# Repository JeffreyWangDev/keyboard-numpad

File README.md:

# Keyboard PCB Repository

This contains files and resources to design and build custom keyboard PCBs using KiCad.

## Getting Started

1. **Clone the Repository**:
    ```sh
    git clone https://github.com/jeffreywangdev/keyboard-numpad.git
    cd keyboard-numpad
    ```
2. **Install KiCad**: Ensure the latest version is installed.
3. **Open the Project**: Open the `.kicad_pro` file.
4. **Explore the Libraries**: Check out the footprint libraries and 3D models.

## Directory Structure

```
keyboard-numpad/
├── 3dmodels/                # 3D models
├── footprints/              # Footprint libraries
├── symbols/                 # Symbol libraries
├── docs/                    # Documentation
```

## Contributing

1. **Fork the Repository**: On GitHub.
2. **Create a Branch**:
    ```sh
    git checkout -b feature-name
    ```
3. **Make Changes**: Commit with descriptive messages.
4. **Submit a Pull Request**: Merge changes into the main repository.

## License

Licensed under the MIT License. See the [LICENSE](LICENSE) file.

Happy designing!

## Code
https://github.com/JeffreyWangDev/qmk_firmware/commit/e154b066790265e3da3770a5a3616bc74e3c47f7#diff-a4a6e8d4f2de04b7d767e970e2a342e9860d40d9419f873e876addc308344293

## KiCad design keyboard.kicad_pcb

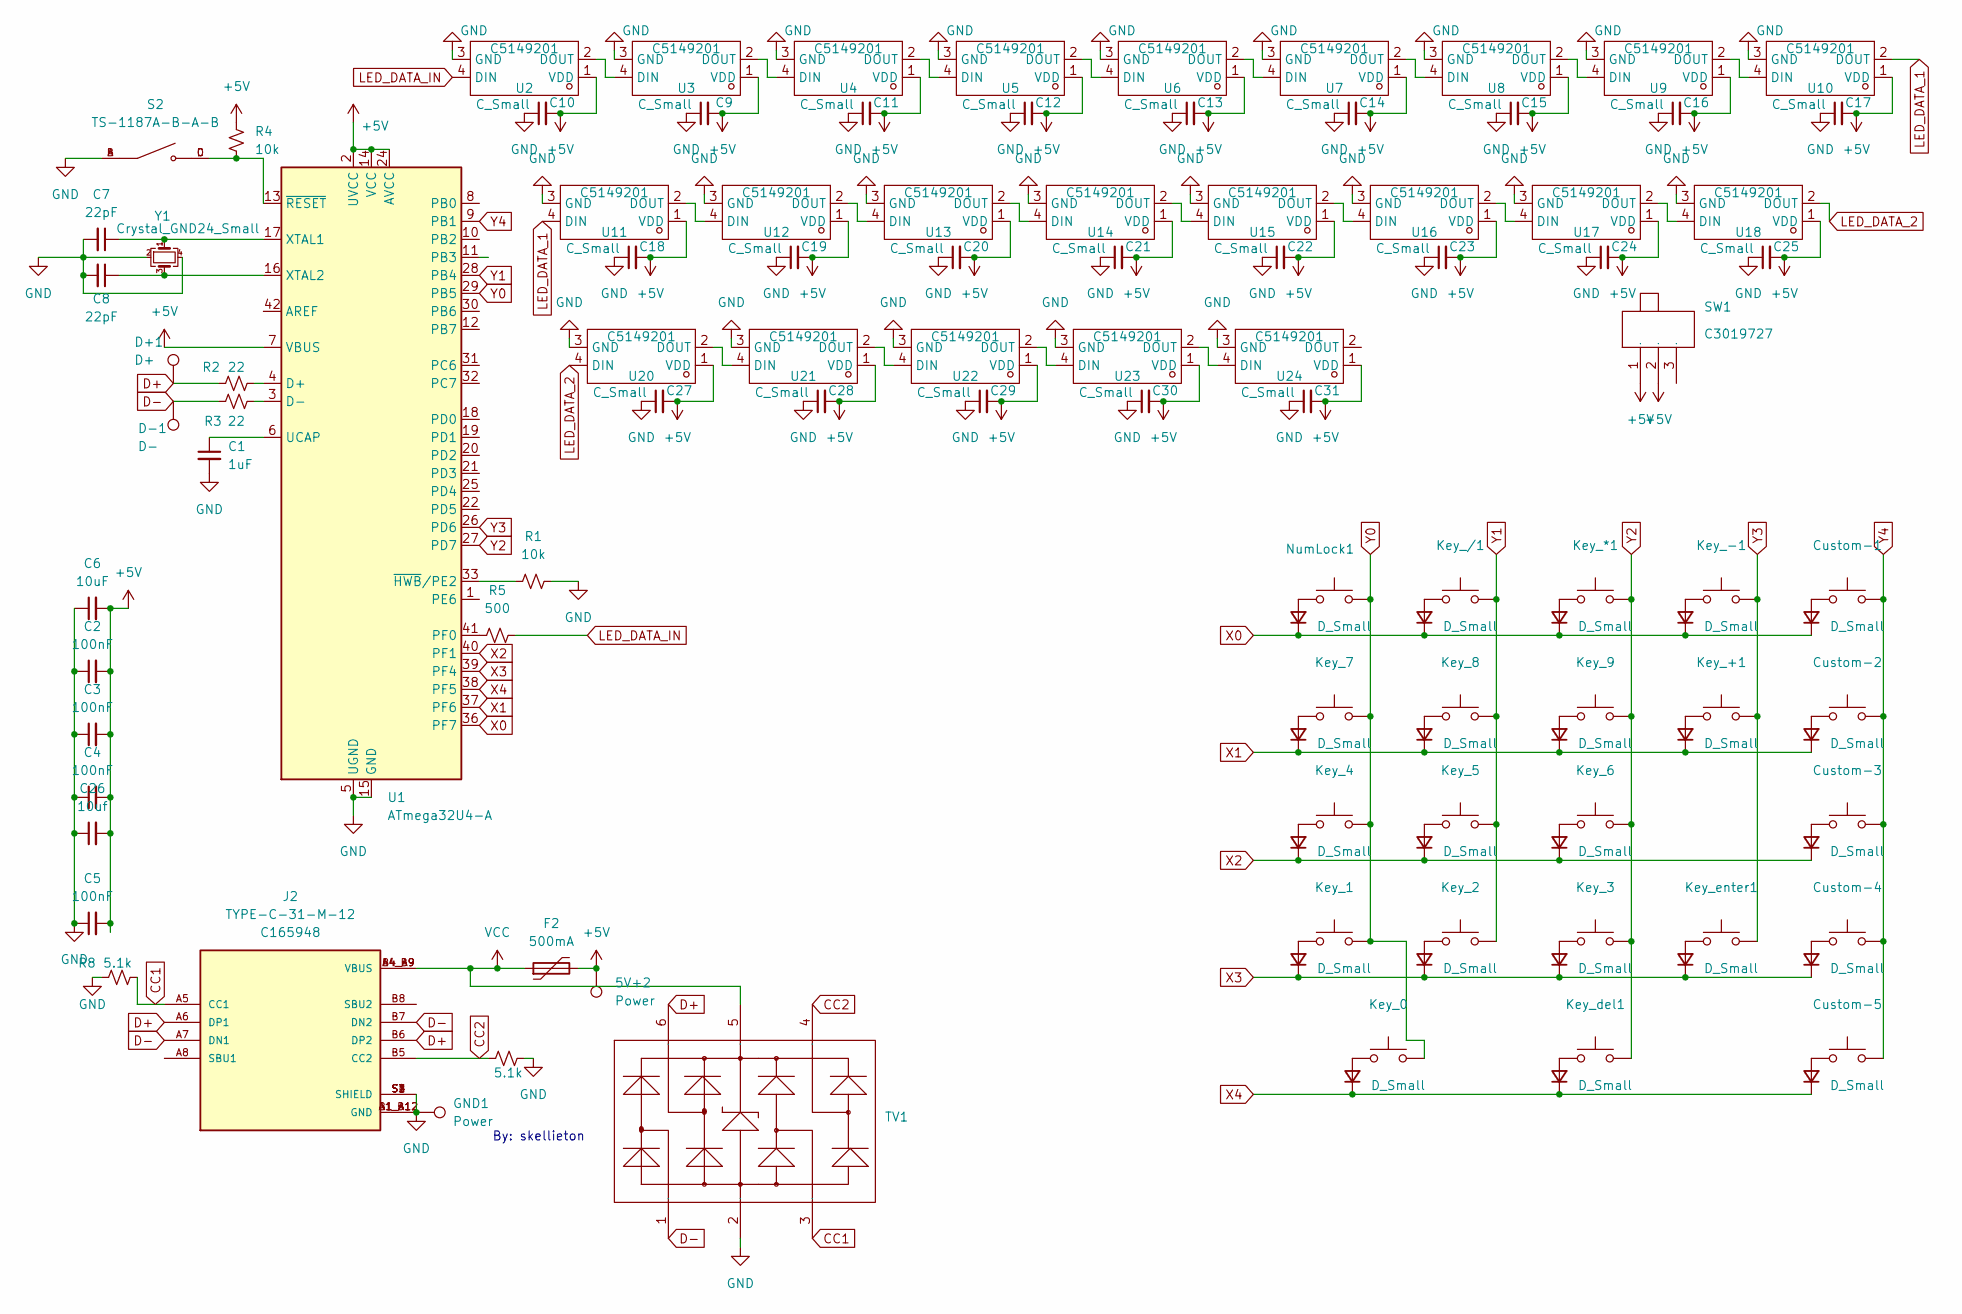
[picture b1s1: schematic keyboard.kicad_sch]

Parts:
5V+2: Power; TestPoint_Pad_1.0x1.0mm
C1: 1uF; C_0805_2012Metric; LCSC C28323
C2, C3, C4: 100nF; C_0805_2012Metric; LCSC C49678
C5: 100nF; C_0805_2012Metric
C6: 10uF; C_0805_2012Metric; LCSC C15850
C7: 22pF; C_0805_2012Metric; LCSC C1804
C8: 22pF; C_0805_2012Metric
C9, C11, C12, C13, C14, C15, C16, C17, C18, C19, C20, C21, C22, C23, C24, C25, C27, C28, C29, C30, C31: C_Small; C_0805_2012Metric
C10: C_Small; C_0805_2012Metric; LCSC C49678
C26: 10uf; C_0805_2012Metric; LCSC C15850
Custom-1, Custom-2, Custom-3, Custom-4, Custom-5: SW_Push; MX-Hotswap-1U
D1, D2: D_Small; D_SOD-123; LCSC C64898
D3, D4, D5, D6, D7, D8, D9, D10, D11, D12, D13, D14, D16, D17, D18, D19, D20, D21, D23, D25: D_Small; D_SOD-123
D+1: D+; TestPoint_Pad_1.0x1.0mm
D-1: D-; TestPoint_Pad_1.0x1.0mm
F2: 500mA; Fuse_1206_3216Metric; LCSC C70076
GND1: Power; TestPoint_Pad_1.0x1.0mm
J2: TYPE-C-31-M-12; HRO_TYPE-C-31-M-12; LCSC C165948
Key_0: SW_Push_U2; MX-Hotswap-2U-ReversedStabilizers
Key_1, Key_2, Key_3, Key_4, Key_5, Key_6, Key_7, Key_8, Key_9: SW_Push; MX-Hotswap-1U
Key_*1: SW_Push; MX-Hotswap-1U
Key_+1: SW_Push_U2; MX-Hotswap-2U-ReversedStabilizers
Key_-1: SW_Push; MX-Hotswap-1U
Key_/1: SW_Push; MX-Hotswap-1U
Key_del1: SW_Push; MX-Hotswap-1U
Key_enter1: SW_Push_U2; MX-Hotswap-2U-ReversedStabilizers
NumLock1: SW_Push; MX-Hotswap-1U; LCSC C41430893
R1, R4: 10k; R_0805_2012Metric; LCSC C17414
R2, R3: 22; R_0805_2012Metric; LCSC C17561
R5: 500; R_0805_2012Metric
R7, R8: 5.1k; R_0805_2012Metric; LCSC C27834
S2: TS-1187A-B-A-B; SW_TS-1187A-B-A-B
SW1: SW-TH_MK-12D18-G040; Manufacturer Part MK-12D18-G020; LCSC Part Name 边三脚微型拨动开关G4
TV1: SOT-23-6_L2.9-W1.6-P0.95-LS2.8-BR; Manufacturer Part SRV05-4-P-T7; LCSC Part Name SRV05-4-P-T7
U1: ATmega32U4-A; TQFP-44_10x10mm_P0.8mm
U2, U3, U4, U5, U6, U12, U13, U14, U15, U22, U23, U24: MX-SK-E-Left_Right; Manufacturer Part SK6812MINI-E; LCSC Part Name SK6812MINI-E
U7, U8, U9, U10, U11, U16, U17, U18, U20, U21: MX-SK-E-Right_Left; Manufacturer Part SK6812MINI-E; LCSC Part Name SK6812MINI-E
Y1: Crystal_GND24_Small; Crystal_SMD_3225-4Pin_3.2x2.5mm; LCSC C13738

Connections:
CC1: J2.A5 (CC1), R8.2, TV1.3
CC2: J2.B5 (CC2), R7.2, TV1.4
D+: D+1.1, J2.A6 (DP1), J2.B6 (DP2), R2.2, TV1.6
D-: D-1.1, J2.A7 (DN1), J2.B7 (DN2), R3.1, TV1.1
GND: C1.2, C2.1, C3.1, C4.1, C5.1, C6.1, C7.2, C8.2, C9.1, C10.1, C11.1, C12.1, C13.1, C14.1, C15.1, C16.1, C17.1, C18.1, C19.1, C20.1, C21.1, C22.1, C23.1, C24.1, C25.1, C26.1, C27.1, C28.1, C29.1, C30.1, C31.1, GND1.1, J2.A1_B12 (GND), J2.B1_A12 (GND), J2.S1 (SHIELD), J2.S2 (SHIELD), J2.S3 (SHIELD), J2.S4 (SHIELD), R1.2, R7.1, R8.1, S2.A, S2.B, TV1.2, U1.5 (UGND), U1.15 (GND), U1.23 (GND), U1.35 (GND), U1.43 (GND), U2.3 (GND), U3.3 (GND), U4.3 (GND), U5.3 (GND), U6.3 (GND), U7.3 (GND), U8.3 (GND), U9.3 (GND), U10.3 (GND), U11.3 (GND), U12.3 (GND), U13.3 (GND), U14.3 (GND), U15.3 (GND), U16.3 (GND), U17.3 (GND), U18.3 (GND), U20.3 (GND), U21.3 (GND), U22.3 (GND), U23.3 (GND), U24.3 (GND), Y1.2, Y1.4
LED_DATA_1: U10.2 (DOUT), U11.4 (DIN)
LED_DATA_2: U18.2 (DOUT), U20.4 (DIN)
LED_DATA_IN: R5.2, U2.4 (DIN)
unnamed: D1.2 (A), NumLock1.1
unnamed: D2.2 (A), Key_/1.1
unnamed: D3.2 (A), Key_7.1
unnamed: D4.2 (A), Key_8.1
unnamed: D5.2 (A), Key_4.1
unnamed: D6.2 (A), Key_1.1
unnamed: D7.2 (A), Key_5.1
unnamed: D8.2 (A), Key_2.1
unnamed: D9.2 (A), Key_*1.1
unnamed: D10.2 (A), Key_9.1
unnamed: D11.2 (A), Key_-1.1
unnamed: D12.2 (A), Key_+1.1
unnamed: D13.2 (A), Key_6.1
unnamed: D14.2 (A), Key_3.1
unnamed: D16.2 (A), Key_enter1.1
unnamed: Custom-1.1, D17.2 (A)
unnamed: Custom-2.1, D18.2 (A)
unnamed: Custom-3.1, D19.2 (A)
unnamed: Custom-4.1, D20.2 (A)
unnamed: D21.2 (A), Key_0.1
unnamed: D23.2 (A), Key_del1.1
unnamed: Custom-5.1, D25.2 (A)
unnamed: R2.1, U1.4 (D+)
unnamed: R3.2, U1.3 (D-)
unnamed: R5.1, U1.41 (PF0)
unnamed: C1.1, U1.6 (UCAP)
unnamed: C7.1, U1.17 (XTAL1), Y1.1
unnamed: C8.1, U1.16 (XTAL2), Y1.3
unnamed: R1.1, U1.33 (~HWB/PE2)
unnamed: R4.2, S2.C, S2.D, U1.13 (~RESET)
unnamed: U2.2 (DOUT), U3.4 (DIN)
unnamed: U3.2 (DOUT), U4.4 (DIN)
unnamed: U4.2 (DOUT), U5.4 (DIN)
unnamed: U5.2 (DOUT), U6.4 (DIN)
unnamed: U6.2 (DOUT), U7.4 (DIN)
unnamed: U7.2 (DOUT), U8.4 (DIN)
unnamed: U8.2 (DOUT), U9.4 (DIN)
unnamed: U9.2 (DOUT), U10.4 (DIN)
unnamed: U11.2 (DOUT), U12.4 (DIN)
unnamed: U12.2 (DOUT), U13.4 (DIN)
unnamed: U13.2 (DOUT), U14.4 (DIN)
unnamed: U14.2 (DOUT), U15.4 (DIN)
unnamed: U15.2 (DOUT), U16.4 (DIN)
unnamed: U16.2 (DOUT), U17.4 (DIN)
unnamed: U17.2 (DOUT), U18.4 (DIN)
unnamed: U20.2 (DOUT), U21.4 (DIN)
unnamed: U21.2 (DOUT), U22.4 (DIN)
unnamed: U22.2 (DOUT), U23.4 (DIN)
unnamed: U23.2 (DOUT), U24.4 (DIN)
VCC: F2.1, J2.A4_B9 (VBUS), J2.B4_A9 (VBUS), TV1.5
X0: D1.1 (K), D2.1 (K), D9.1 (K), D11.1 (K), D17.1 (K), U1.36 (PF7)
Y0: Key_0.2, Key_1.2, Key_4.2, Key_7.2, NumLock1.2, U1.29 (PB5)
Y1: Key_2.2, Key_5.2, Key_8.2, Key_/1.2, U1.28 (PB4)
Y2: Key_3.2, Key_6.2, Key_9.2, Key_*1.2, Key_del1.2, U1.27 (PD7)
Y3: Key_+1.2, Key_-1.2, Key_enter1.2, U1.26 (PD6)
Y4: Custom-1.2, Custom-2.2, Custom-3.2, Custom-4.2, Custom-5.2, U1.9 (PB1)

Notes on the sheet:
By: skellieton

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
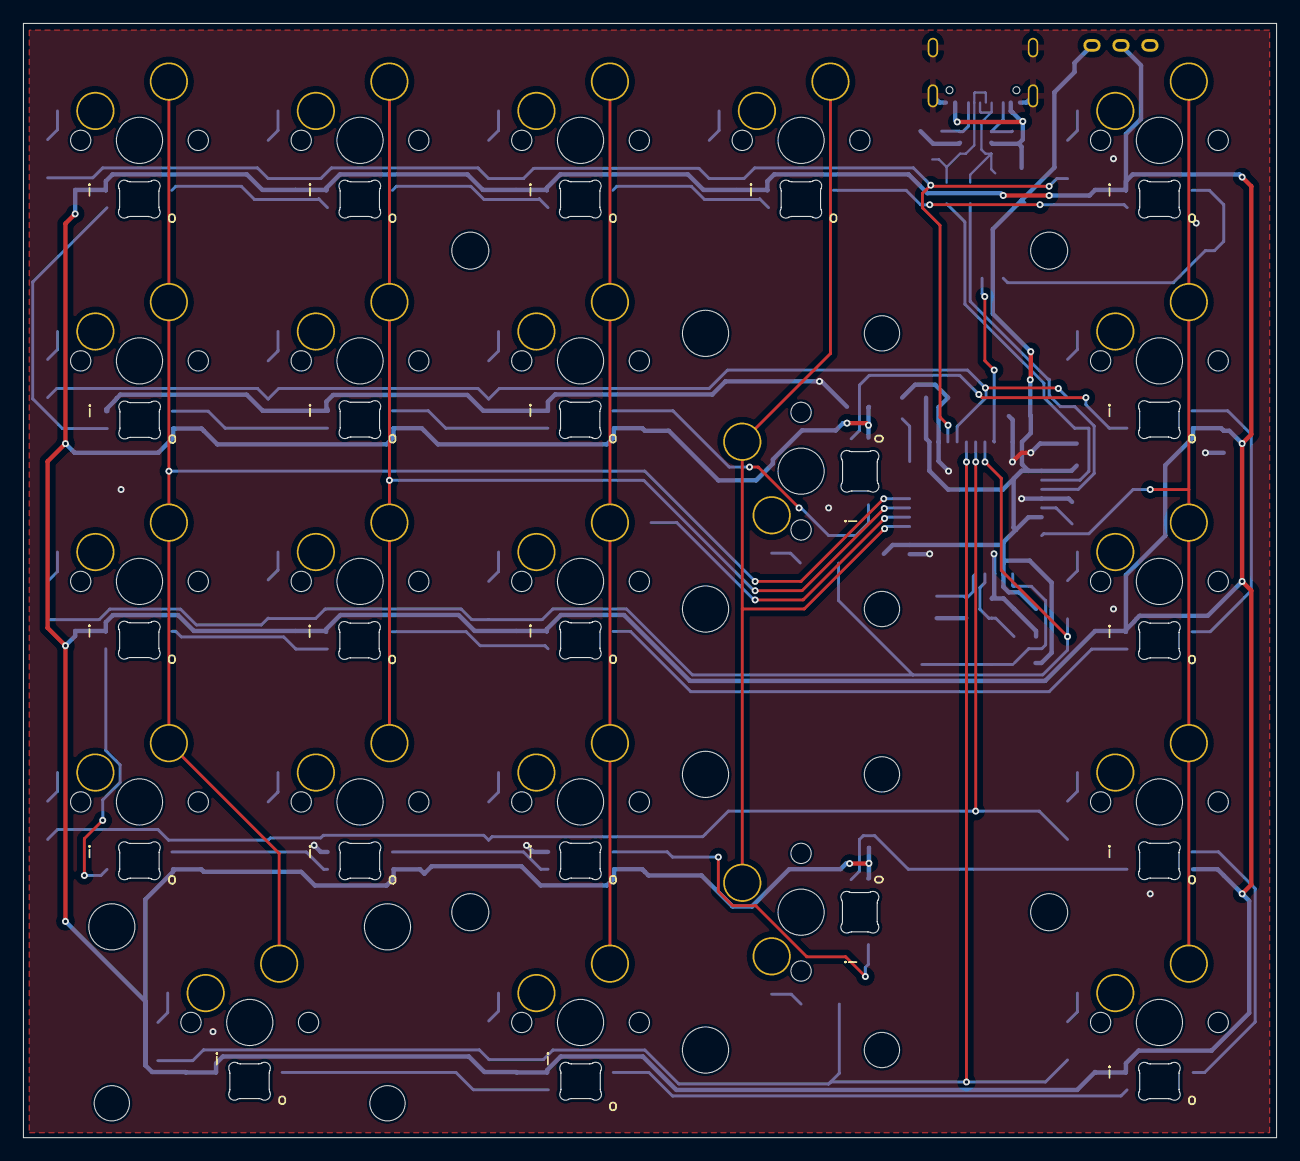
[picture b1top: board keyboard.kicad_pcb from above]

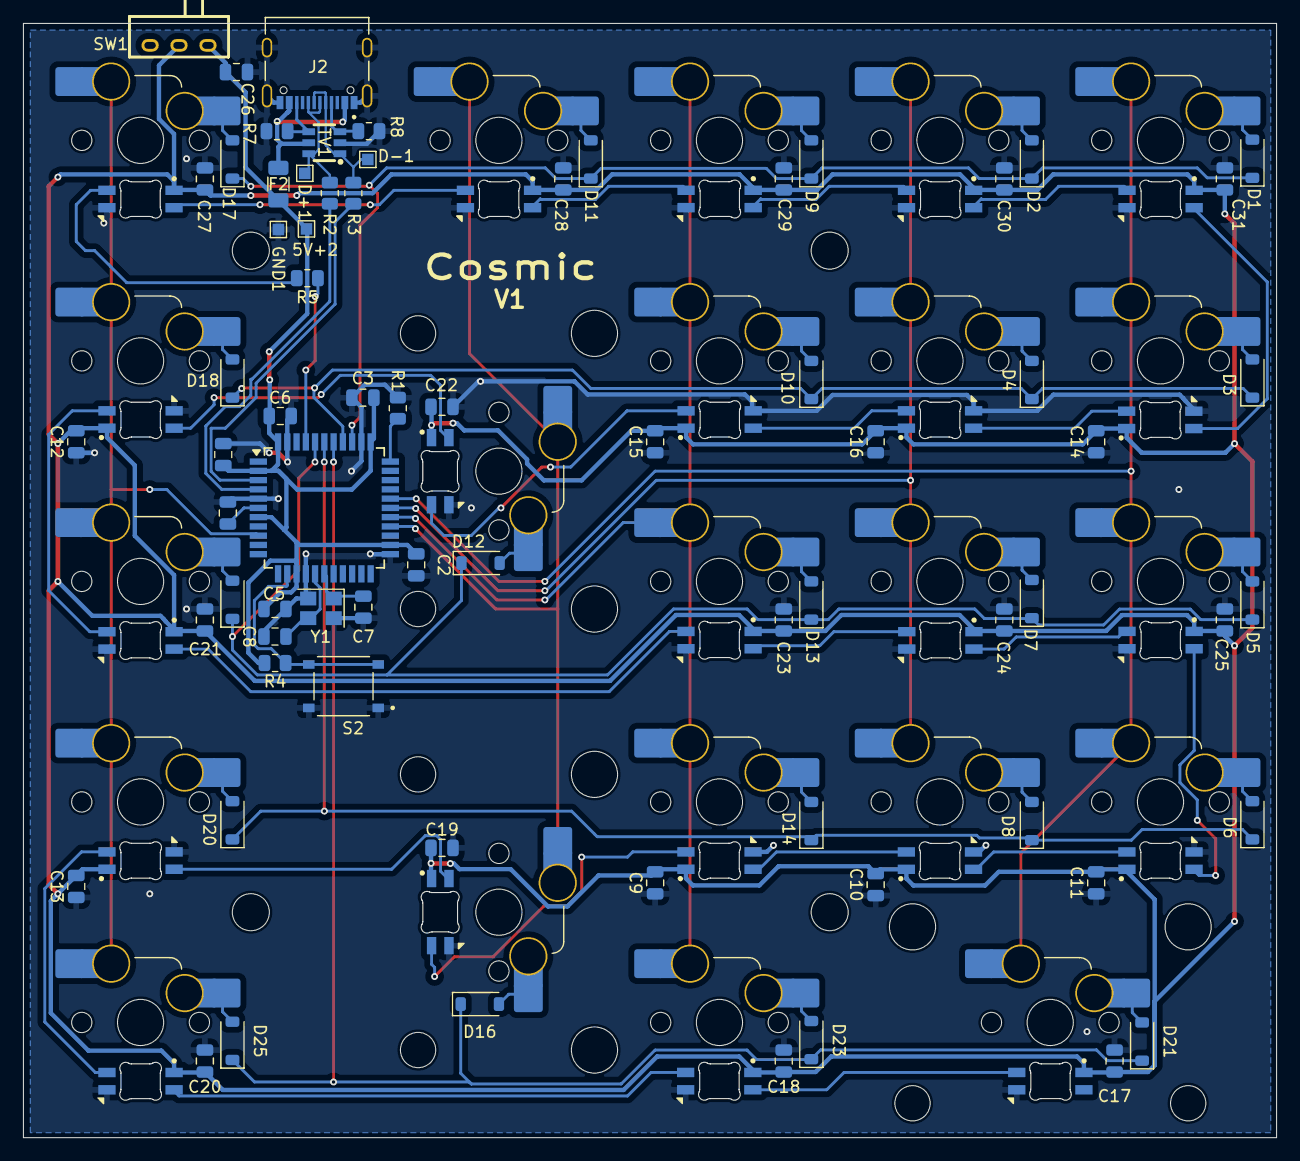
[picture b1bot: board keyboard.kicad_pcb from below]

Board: 2 copper layers, 108.2 x 96.2 mm, 122 parts (115 on the bottom side), 70 nets.

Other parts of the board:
H1, H2, H3, H4: MountingHole; MountingHole_3.2mm_M3
H5, H6, H7: MountingHole; STAB_MX_2u

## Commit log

2024-11-21 libs
2024-11-23 step
2024-11-24 fixFlip
2024-11-24 V1-with-led-schem
2024-11-24 V2-led
2024-11-24 V2.1, used a grounding plane
2024-11-24 upaded islands
2024-11-25 added switch
